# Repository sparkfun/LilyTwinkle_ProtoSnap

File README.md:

LilyTwinkle ProtoSnap
=====================

[*SparkFun LilyTwinkle ProtoSnap (DEV-11590)*](https://www.sparkfun.com/products/11590)

The ProtoSnap LilyTwinkle board is a very simple way to jump right into e-textiles. By including the LilyTwinkle, a 
coin cell battery holder (with built-in switch), and four white LEDs the ProtoSnap LilyTwinkle board easily allows 
you to add some sparkle to any project.

Repository Contents
-------------------
* **/Hardware** - All Eagle design files (.brd, .sch)
* **/Production** - Test bed files and production panel files

Documentation
--------------

* Getting Started Tutorials
  * **[LDK Experiment 6: Microcontroller Circuits](https://learn.sparkfun.com/tutorials/ldk-experiment-6-microcontroller-circuits)**
  * **[Using the LilyPad LilyTwinkle board](https://www.sparkfun.com/tutorials/390)**
* Project Tutorials -- Example projects using the LilyTiny and LilyTwinkle
  * **[Twinkle Zodiac Constellation](https://learn.sparkfun.com/tutorials/twinkle-zodiac-constellation)**
  * **[Night Sky Halloween Costume](https://learn.sparkfun.com/tutorials/night-sky-halloween-costume)**
  * **[Firefly Jar Assembly Guide](https://learn.sparkfun.com/tutorials/firefly-jar-assembly-guide)** 
  * **[Soft Circuits: LED Feelings Pizza](https://learn.sparkfun.com/tutorials/soft-circuits-led-feelings-pizza)**
  * **[Twinkling Trick or Treat Bag](https://learn.sparkfun.com/tutorials/twinkling-trick-or-treat-bag)**
  * **[Light Up Pennant with E-Textiles](https://learn.sparkfun.com/tutorials/light-up-pennant-with-e-textiles)**
  * **[LilyTiny Plush Monster](https://learn.sparkfun.com/tutorials/lilytiny-plush-monster)**
  * **[Twinkling Fairy Wings](https://www.sparkfun.com/tutorials/396)**
* **[Re-Programming the LilyTiny / LilyTwinkle](https://learn.sparkfun.com/tutorials/re-programming-the-lilytiny--lilytwinkle)** - Tutorial to reprogram the LilyTiny or LilyTwinkle.
* **[Quick Reference Guide for ATTiny85](https://learn.sparkfun.com/resources/96)**

License Information
-------------------
The hardware is released under [Creative Commons ShareAlike 4.0 International](https://creativecommons.org/licenses/by-sa/4.0/).
The code is beerware; if you see me (or any other SparkFun employee) at the local, and you've found our code helpful, please buy us a round!

Distributed as-is; no warranty is given.

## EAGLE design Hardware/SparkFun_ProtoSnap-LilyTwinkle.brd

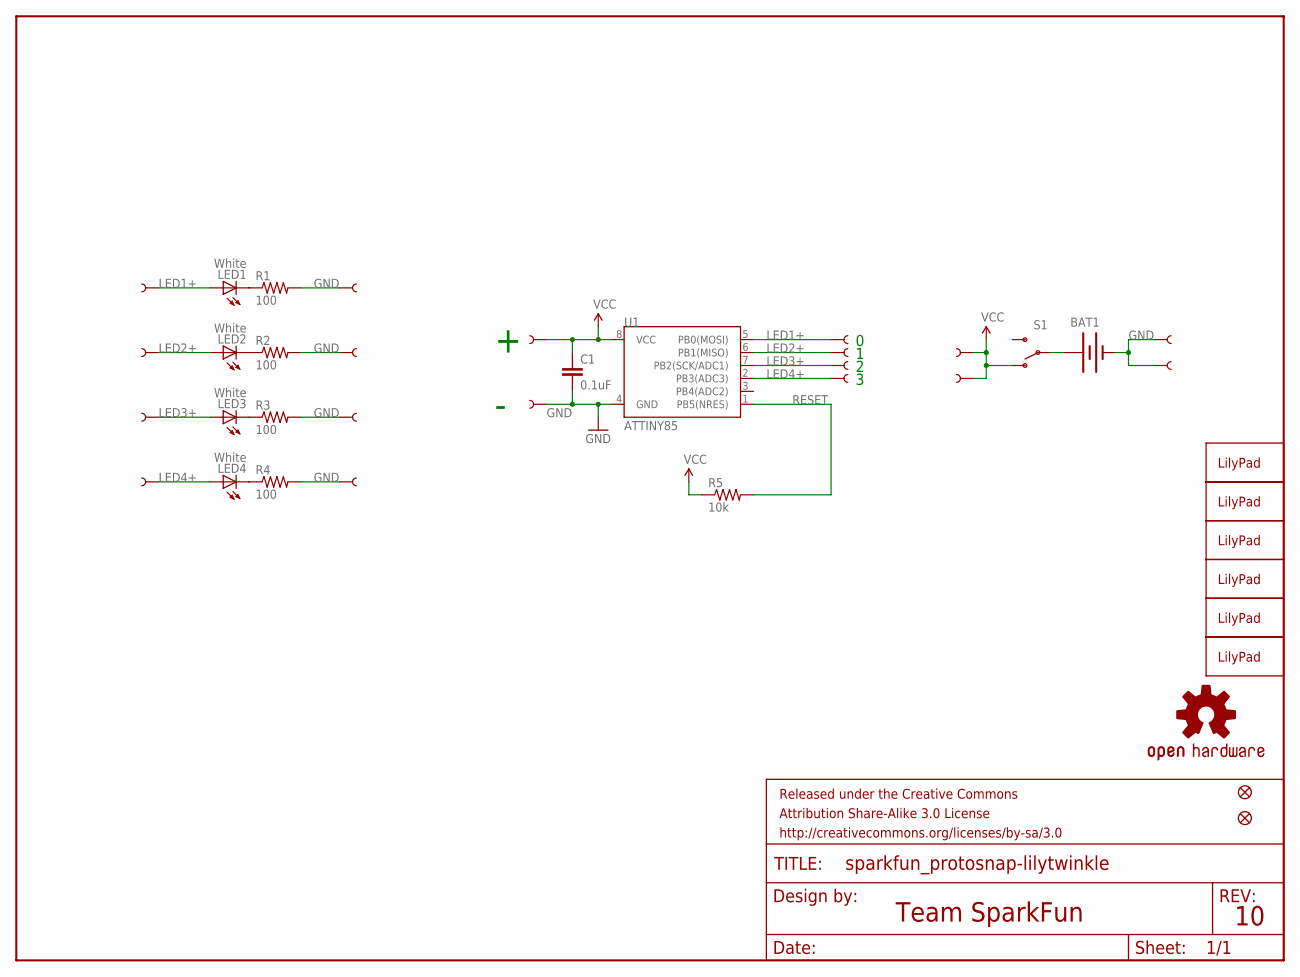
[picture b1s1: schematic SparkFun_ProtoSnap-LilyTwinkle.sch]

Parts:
1_U$2, 1_U$3, 1_U$4, 1_U$5, 1_U$6, 1_U$7: SEWTAP6; PETAL-SMALL-2SIDE
3_LED+, 3_LED-, 4_LED+, 4_LED-, 5_LED+, 5_LED-, 6_LED+, 6_LED-: SEWTAP6; PETAL-SMALL
B1+, B1-, B2+, B2-: SEWTAP6; PETAL-SMALL-2SIDE
BAT1: BATTERY20MM_4LEGS; BATTCON_20MM_4LEGS
BATT_LOGO: LOGO-LPLP; LOGO-LILYPAD
BATT_OHS: OSHW-LOGOS; OSHW-LOGO-S
C1: 0.1uF; 0402-CAP
FRAME1: FRAME-LETTER; CREATIVE_COMMONS
JP1, JP2: FIDUCIALUFIDUCIAL; MICRO-FIDUCIAL
LED1, LED2, LED3, LED4: White; LED-1206
LED1_LOGO, LED2_LOGO, LED3_LOGO, LED4_LOGO: LOGO-LPL; LOGO-L
R1, R2, R3, R4: 100; 0603-RES
R5: 10k; 0402-RES
S1: SWITCH-SPDTSMD; AYZ0202
TINY_LOGO: LOGO-LPL; LOGO-L
U1: ATTINY85; SO08-EIAJ

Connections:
2_N$3: BAT1.1 (+), S1.2
3_N$1: LED3.C, R3.1
4_N$1: LED4.C, R4.1
5_N$1: LED2.C, R2.1
6_N$1: LED1.C, R1.1
GND: 1_U$2.1, 3_LED-.1, 4_LED-.1, 5_LED-.1, 6_LED-.1, B1-.1, B2-.1, BAT1.2 (-), C1.2, R1.2, R2.2, R3.2, R4.2, U1.4 (GND)
LED1+: 1_U$7.1, 6_LED+.1, LED1.A, U1.5 (PB0(MOSI))
LED2+: 1_U$3.1, 5_LED+.1, LED2.A, U1.6 (PB1(MISO))
LED3+: 1_U$4.1, 3_LED+.1, LED3.A, U1.7 (PB2(SCK/ADC1))
LED4+: 1_U$6.1, 4_LED+.1, LED4.A, U1.2 (PB3(ADC3))
RESET: R5.2, U1.1 (PB5(NRES))
V+: 1_U$5.1, B1+.1, B2+.1, C1.1, R5.1, S1.1 (O), U1.8 (VCC)

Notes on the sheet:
Team SparkFun

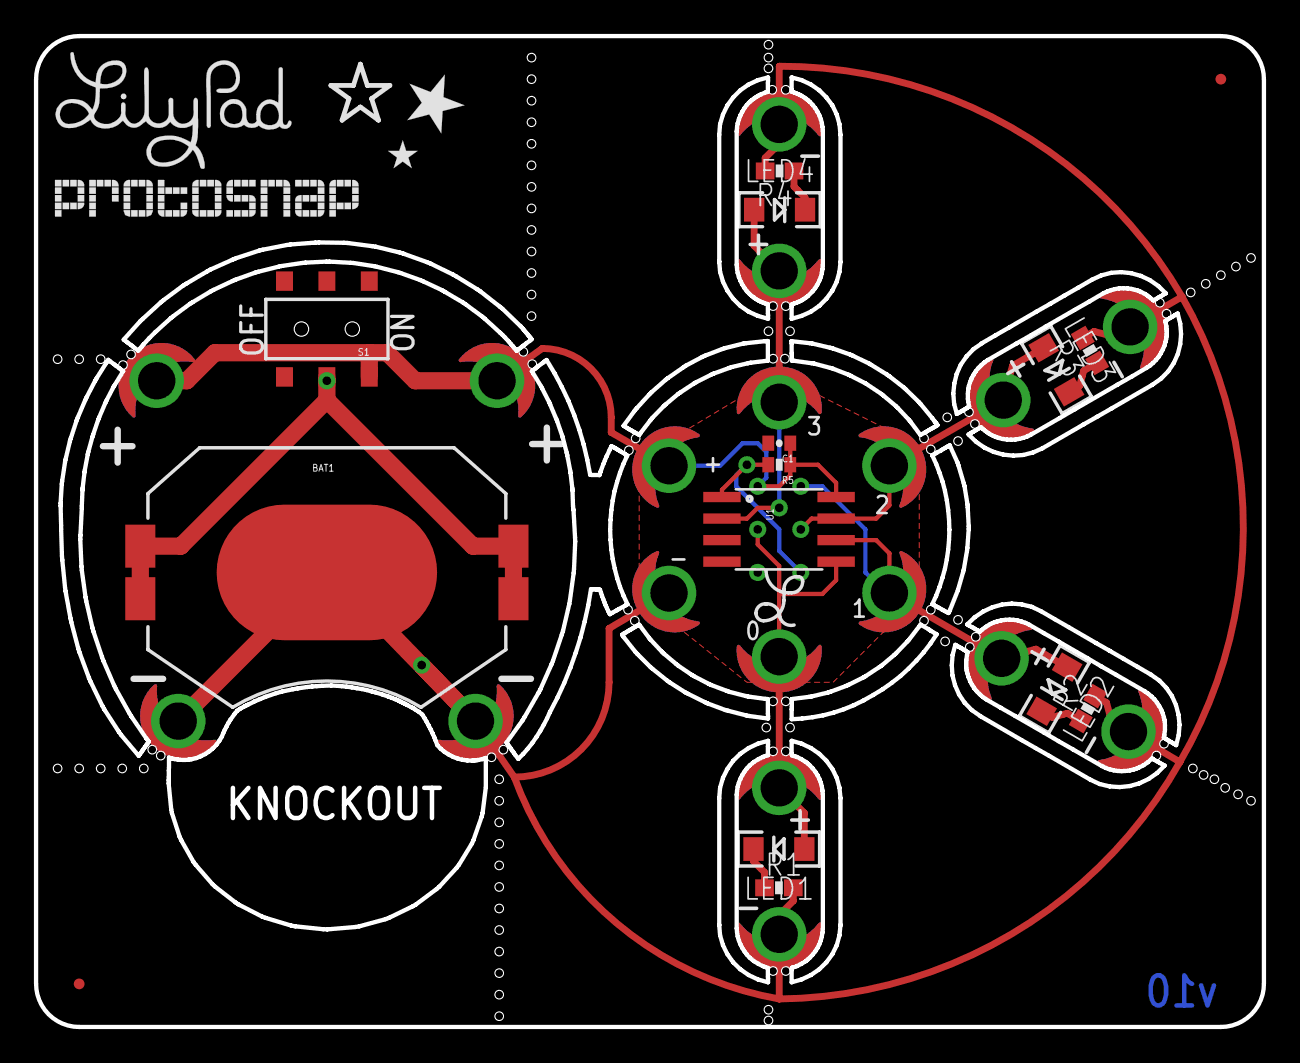
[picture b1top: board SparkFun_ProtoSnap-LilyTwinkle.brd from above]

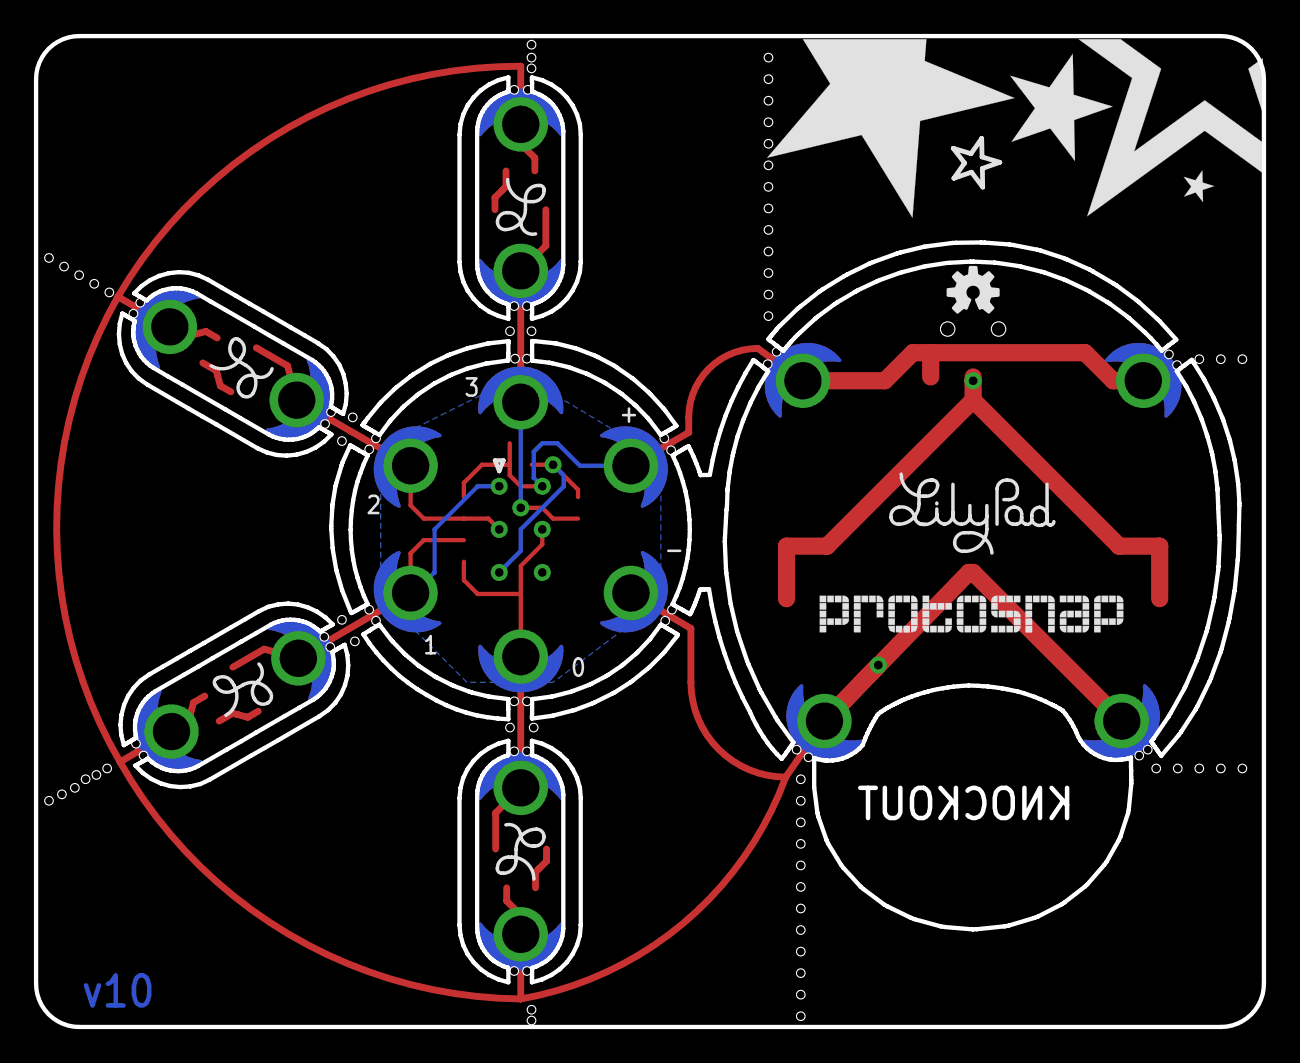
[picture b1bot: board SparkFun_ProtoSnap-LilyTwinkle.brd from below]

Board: 2 copper layers, 72.4 x 58.4 mm, 41 parts (6 on the bottom side), 12 nets.

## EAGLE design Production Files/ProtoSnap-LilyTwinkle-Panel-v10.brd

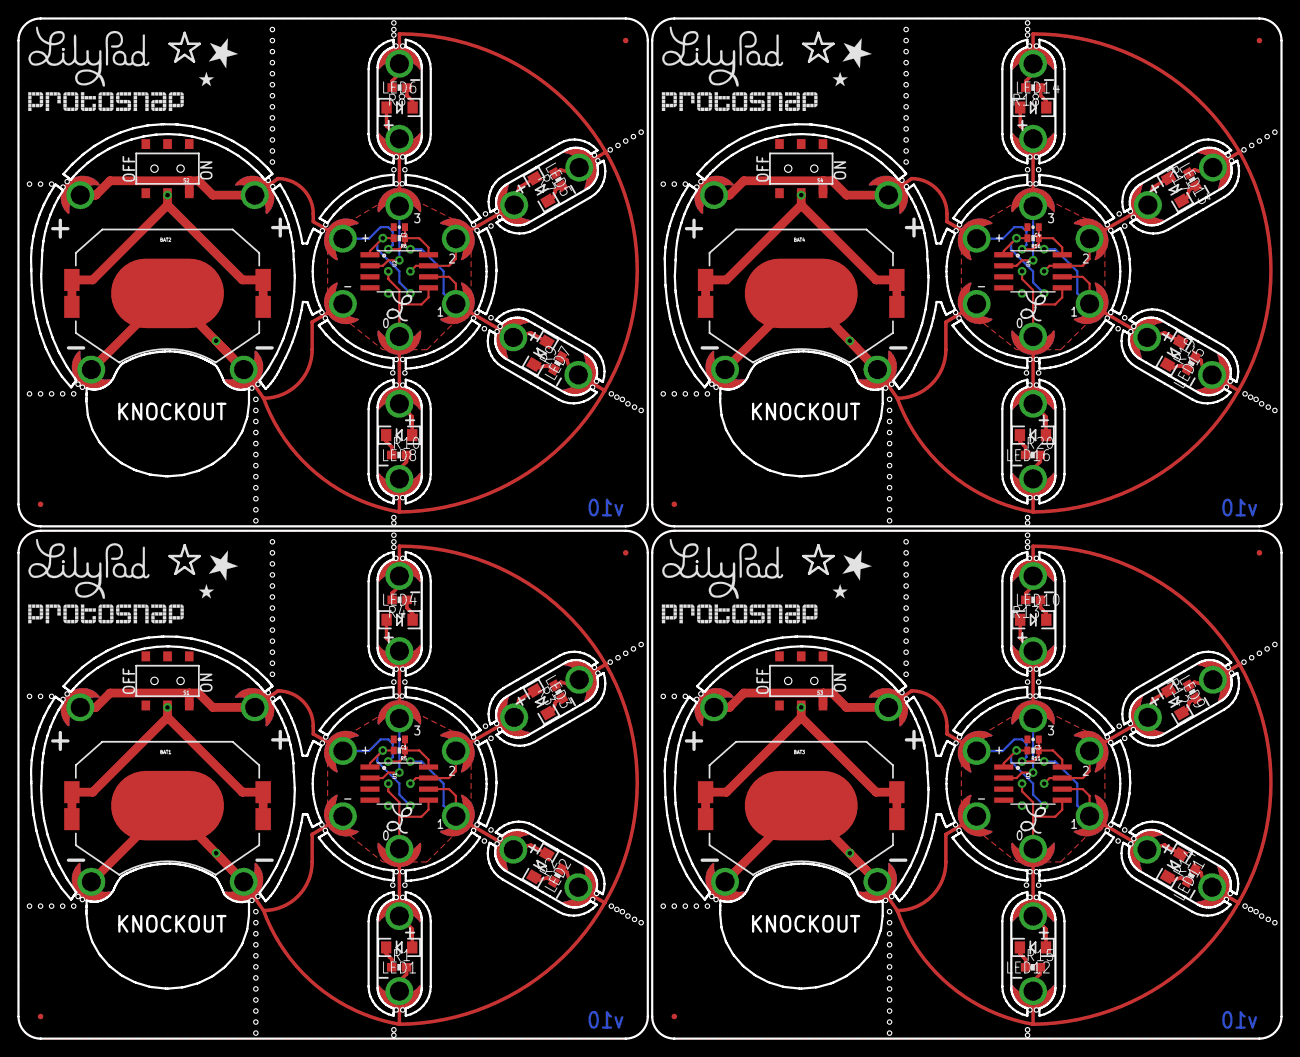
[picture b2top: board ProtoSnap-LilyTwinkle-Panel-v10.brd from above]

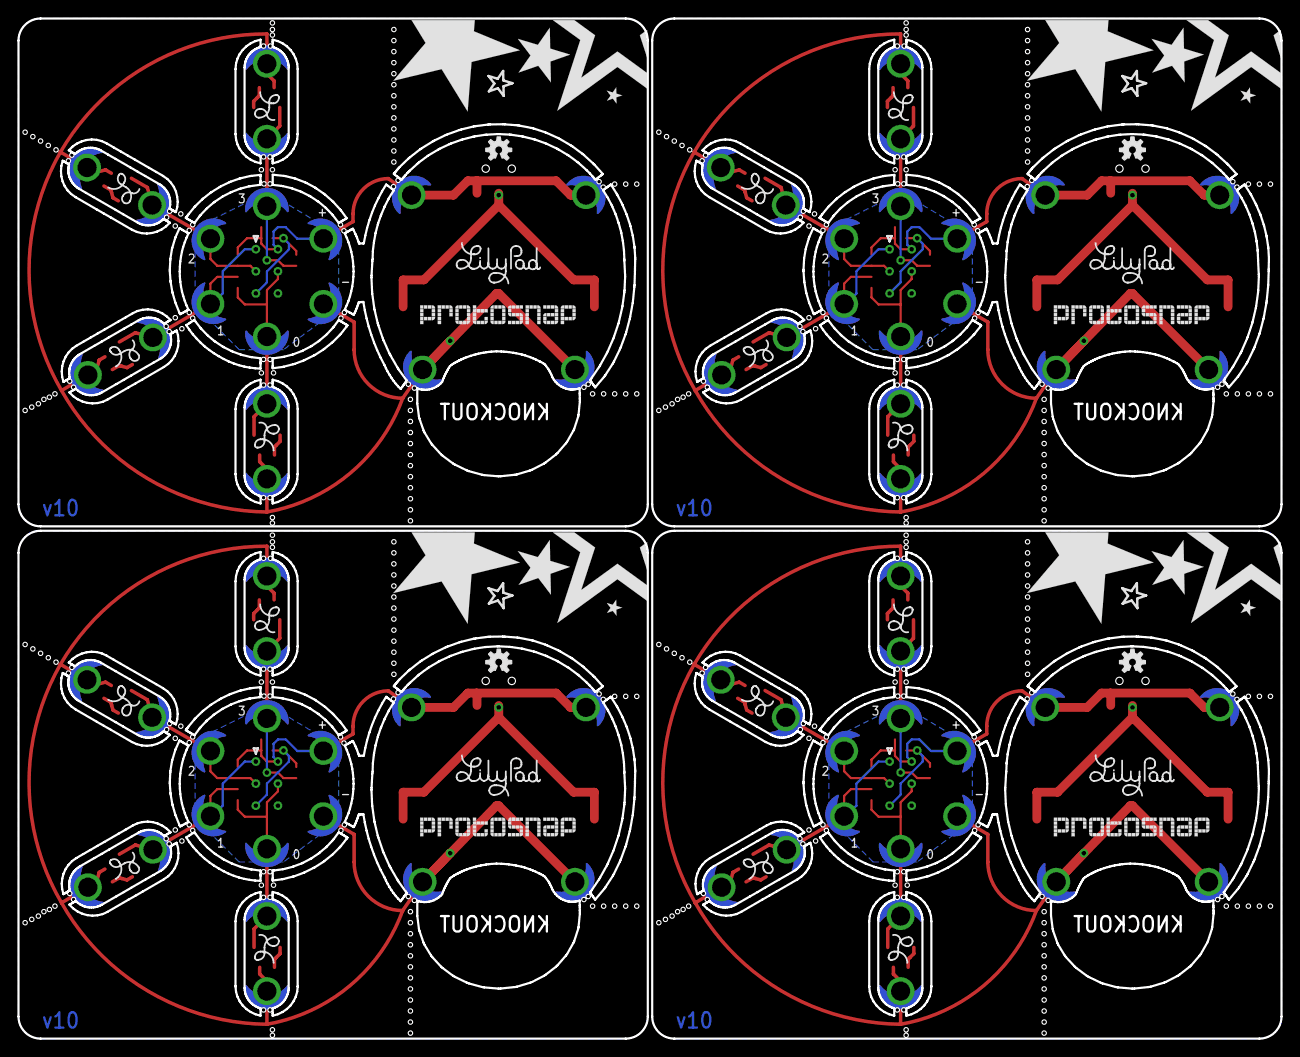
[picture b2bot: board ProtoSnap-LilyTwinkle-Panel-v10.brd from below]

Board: 2 copper layers, 145.3 x 117.3 mm, 160 parts (24 on the bottom side), 48 nets.

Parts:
1_U$1, 1_U$2, 1_U$3, 1_U$4, 1_U$5, 1_U$6, 1_U$7, 1_U$8, 1_U$9, 1_U$10, 1_U$11, 1_U$12, 1_U$13, 1_U$14, 1_U$15, 1_U$16, 1_U$17, 1_U$18, 1_U$19, 1_U$20, 1_U$21, 1_U$22, 1_U$23, 1_U$24: SEWTAP6; PETAL-SMALL-2SIDE
3_LED+, 3_LED+1, 3_LED+2, 3_LED+3, 3_LED-, 3_LED-1, 3_LED-2, 3_LED-3, 4_LED+, 4_LED+1, 4_LED+2, 4_LED+3, 4_LED-, 4_LED-1, 4_LED-2, 4_LED-3, 5_LED+, 5_LED+1, 5_LED+2, 5_LED+3, 5_LED-, 5_LED-1, 5_LED-2, 5_LED-3, 6_LED+, 6_LED+1, 6_LED+2, 6_LED+3, 6_LED-, 6_LED-1, 6_LED-2, 6_LED-3: SEWTAP6; PETAL-SMALL
B1+, B1+1, B1+2, B1+3, B1-, B1-1, B1-2, B1-3, B2+, B2+1, B2+2, B2+3, B2-, B2-1, B2-2, B2-3: SEWTAP6; PETAL-SMALL-2SIDE
BAT1, BAT2, BAT3, BAT4: BATTCON_20MM_4LEGS
BATT_LOGO, BATT_LOGO1, BATT_LOGO2, BATT_LOGO3: LOGO-LPLP; LOGO-LILYPAD
BATT_OHS, BATT_OHS1, BATT_OHS2, BATT_OHS3: OSHW-LOGOS; OSHW-LOGO-S
C1, C2, C3, C4: 0.1uF; 0402-CAP
JP1, JP2, JP3, JP4, JP5, JP6, JP7, JP8: FIDUCIALUFIDUCIAL; MICRO-FIDUCIAL
LED1, LED2, LED3, LED4, LED5, LED6, LED7, LED8, LED9, LED10, LED11, LED12, LED13, LED14, LED15, LED16: White; LED-1206
LED1_LOGO, LED1_LOGO1, LED1_LOGO2, LED1_LOGO3, LED2_LOGO, LED2_LOGO1, LED2_LOGO2, LED2_LOGO3, LED3_LOGO, LED3_LOGO1, LED3_LOGO2, LED3_LOGO3, LED4_LOGO, LED4_LOGO1, LED4_LOGO2, LED4_LOGO3: LOGO-LPL; LOGO-L
R1, R2, R3, R4, R7, R8, R9, R10, R12, R13, R14, R15, R17, R18, R19, R20: 100; 0603-RES
R5, R6, R11, R16: 10k; 0402-RES
S1, S2, S3, S4: AYZ0202
TINY_LOGO, TINY_LOGO1, TINY_LOGO2, TINY_LOGO3: LOGO-LPL; LOGO-L
U1, U2, U3, U4: ATTINY85; SO08-EIAJ

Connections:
2_N$1: BAT2.1, S2.2
2_N$2: BAT3.1, S3.2
2_N$3: BAT1.1, S1.2
2_N$4: BAT4.1, S4.2
3_N$1: LED3.C, R3.1
3_N$2: LED5.C, R7.1
3_N$3: LED9.C, R12.1
3_N$4: LED13.C, R17.1
4_N$1: LED4.C, R4.1
4_N$2: LED6.C, R8.1
4_N$3: LED10.C, R13.1
4_N$4: LED14.C, R18.1
5_N$1: LED2.C, R2.1
5_N$2: LED7.C, R9.1
5_N$3: LED11.C, R14.1
5_N$4: LED15.C, R19.1
6_N$1: LED1.C, R1.1
6_N$2: LED8.C, R10.1
6_N$3: LED12.C, R15.1
6_N$4: LED16.C, R20.1
GND: 1_U$2.1, 3_LED-.1, 4_LED-.1, 5_LED-.1, 6_LED-.1, B1-.1, B2-.1, BAT1.2, C1.2, R1.2, R2.2, R3.2, R4.2, U1.4
GND1: 1_U$1.1, 3_LED-1.1, 4_LED-1.1, 5_LED-1.1, 6_LED-1.1, B1-1.1, B2-1.1, BAT2.2, C2.2, R7.2, R8.2, R9.2, R10.2, U2.4
GND2: 1_U$13.1, 3_LED-2.1, 4_LED-2.1, 5_LED-2.1, 6_LED-2.1, B1-2.1, B2-2.1, BAT3.2, C3.2, R12.2, R13.2, R14.2, R15.2, U3.4
GND3: 1_U$19.1, 3_LED-3.1, 4_LED-3.1, 5_LED-3.1, 6_LED-3.1, B1-3.1, B2-3.1, BAT4.2, C4.2, R17.2, R18.2, R19.2, R20.2, U4.4
LED1+: 1_U$7.1, 6_LED+.1, LED1.A, U1.5
LED1+1: 1_U$12.1, 6_LED+1.1, LED8.A, U2.5
LED1+2: 1_U$18.1, 6_LED+2.1, LED12.A, U3.5
LED1+3: 1_U$24.1, 6_LED+3.1, LED16.A, U4.5
LED2+: 1_U$3.1, 5_LED+.1, LED2.A, U1.6
LED2+1: 1_U$8.1, 5_LED+1.1, LED7.A, U2.6
LED2+2: 1_U$14.1, 5_LED+2.1, LED11.A, U3.6
LED2+3: 1_U$20.1, 5_LED+3.1, LED15.A, U4.6
LED3+: 1_U$4.1, 3_LED+.1, LED3.A, U1.7
LED3+1: 1_U$9.1, 3_LED+1.1, LED5.A, U2.7
LED3+2: 1_U$15.1, 3_LED+2.1, LED9.A, U3.7
LED3+3: 1_U$21.1, 3_LED+3.1, LED13.A, U4.7
LED4+: 1_U$6.1, 4_LED+.1, LED4.A, U1.2
LED4+1: 1_U$11.1, 4_LED+1.1, LED6.A, U2.2
LED4+2: 1_U$17.1, 4_LED+2.1, LED10.A, U3.2
LED4+3: 1_U$23.1, 4_LED+3.1, LED14.A, U4.2
RESET: R5.2, U1.1
RESET1: R6.2, U2.1
RESET2: R11.2, U3.1
RESET3: R16.2, U4.1
V+: 1_U$5.1, B1+.1, B2+.1, C1.1, R5.1, S1.1, U1.8
V+1: 1_U$10.1, B1+1.1, B2+1.1, C2.1, R6.1, S2.1, U2.8
V+2: 1_U$16.1, B1+2.1, B2+2.1, C3.1, R11.1, S3.1, U3.8
V+3: 1_U$22.1, B1+3.1, B2+3.1, C4.1, R16.1, S4.1, U4.8

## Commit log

2012-11-21 V01 commit. These are the files as they went out for protos.
2013-02-12 V10 commit; files as proposed for production. Changes: - BMASK added to programming vias - Pin numbers moved onto masked area on top side - Pin numbers added to bottom - Pin 1 marker added to program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
2013-02-18 Tweaked position of snap holes on battery holder back to where they were. Moved my name to the right place.
2013-02-18 production panel created
    4 board array
2015-01-19 Updating README with product links
2015-02-06 fix gaps in dimension layer

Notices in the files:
parts and their libraries:
2_SparkFun-Aesthetics: Licensing: CC v3.0 Share-Alike You are welcome to use this library for commercial purposes.
SparkFun-Aesthetics: Released under the Creative Commons Attribution Share-Alike 3.0 License
SparkFun-Aesthetics: http://creativecommons.org/licenses/by-sa/3.0
